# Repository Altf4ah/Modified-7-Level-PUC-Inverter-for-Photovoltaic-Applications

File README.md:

# Modified 7-Level PUC Inverter for Photovoltaic Applications

## Overview

This repository presents the design, simulation, and hardware implementation of a **Modified Seven-Level Packed U-Cell (MPUC) Inverter** for photovoltaic applications.

Multilevel inverters are widely used in renewable energy systems to convert DC power generated by solar panels into high-quality AC power suitable for loads or grid integration. Traditional inverter topologies such as Cascaded H-Bridge and Neutral Point Clamped inverters often require a large number of switches and components.

The **Modified Packed U-Cell (MPUC) inverter** provides a compact and efficient alternative by generating multiple voltage levels using fewer components while maintaining high power quality.

This project demonstrates both:

- Simulation validation of the proposed inverter topology
- Hardware implementation of a scaled prototype

---

# Project Objectives

The main objectives of this project are:

- Design a **Modified 7-Level PUC inverter topology**
- Implement **multicarrier SPWM control strategy**
- Validate the system through **simulation**
- Develop a **scaled hardware prototype**
- Analyse output voltage waveform and harmonic distortion

---

# Inverter Topology

The Modified PUC inverter is a **seven-level multilevel inverter topology** that uses:

- Two asymmetrical DC voltage sources
- Six switching devices
- A specialised switching sequence

The topology produces the following output voltage levels:

This multilevel output closely approximates a sinusoidal waveform, reducing harmonic distortion and improving power quality.

---

# Phase 1 — Simulation

The simulation phase validates the proposed inverter design before hardware implementation.

### Tools Used

- MATLAB
- Simulink

### Simulation Components

- MPUC inverter topology
- Multicarrier SPWM generation
- Switching algorithm
- Harmonic analysis

### Simulation Outputs

- 7-level output voltage waveform
- Load current waveform
- FFT analysis
- Total Harmonic Distortion (THD)

---

# Phase 2 — Hardware Implementation

A scaled hardware prototype was developed to validate the inverter performance.

### Hardware Modules

The hardware system consists of three main modules:

### 1. Power Supply Module

- Custom multi-tap transformer
- Bridge rectifier
- Filtering capacitors
- Provides isolated power for gate drivers

### 2. Driver Module

- Optocoupler-based isolation
- Gate driver circuits
- Signal amplification for MOSFET switching

### 3. Inverter Module

- Six MOSFET switches
- Two DC voltage sources
- Converts DC input into multilevel AC output

---

# Hardware Specifications

| Parameter | Value |
|--------|--------|
| Output Voltage | 45 V |
| Output Current | 1 A |
| Switching Devices | IRF540N MOSFET |
| Control Unit | Arduino |
| Driver IC | TLP350 |

---

# Control Strategy

The inverter switching signals are generated using an **Arduino-based control system** implementing a predefined switching table.

This generates the required sequence to produce the **seven-level output waveform**.

---

# PCB Design

The inverter and driver circuits were designed and implemented using:

- PCB layout design
- Copper board etching using ferric chloride
- Component soldering and testing

---

# Results

The results demonstrate that the Modified PUC inverter can generate a multilevel AC waveform with improved quality compared to conventional inverters.

Key outcomes:

- Successful generation of **7-level output voltage**
- Reduced harmonic distortion
- Efficient DC-AC conversion
- Successful hardware validation

---

# Applications

This inverter topology can be applied in:

- Solar photovoltaic systems
- Renewable energy converters
- Microgrid power systems
- Grid-connected inverter systems

---

## Repository Structure

- **Simulation/**
  - MATLAB / Simulink models

- **Hardware/**
  - Driver circuits
  - Inverter circuit
  - PCB design files

- **Arduino_Code/**
  - Switching control program

- **Images/**
  - Circuit diagrams
  - Simulation results
  - Hardware output waveforms

- **Documentation/**
  - Final project report
  - Presentation slides
---

# Authors

Final Year B.Tech Project.  
Department of Electrical Engineering.  
Govt. Model Engineering College, Thrikkakara.

- Althaf Ahmed   
- Daniel Charles  
- Aswathy V  
- Shaun George

---

# License

This project is published for **academic and research purposes**.

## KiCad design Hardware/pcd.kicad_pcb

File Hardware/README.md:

KiCad PCB project for a PUC inverter along with its driver board, designed as a single-layer layout and optimized for DIY etching.

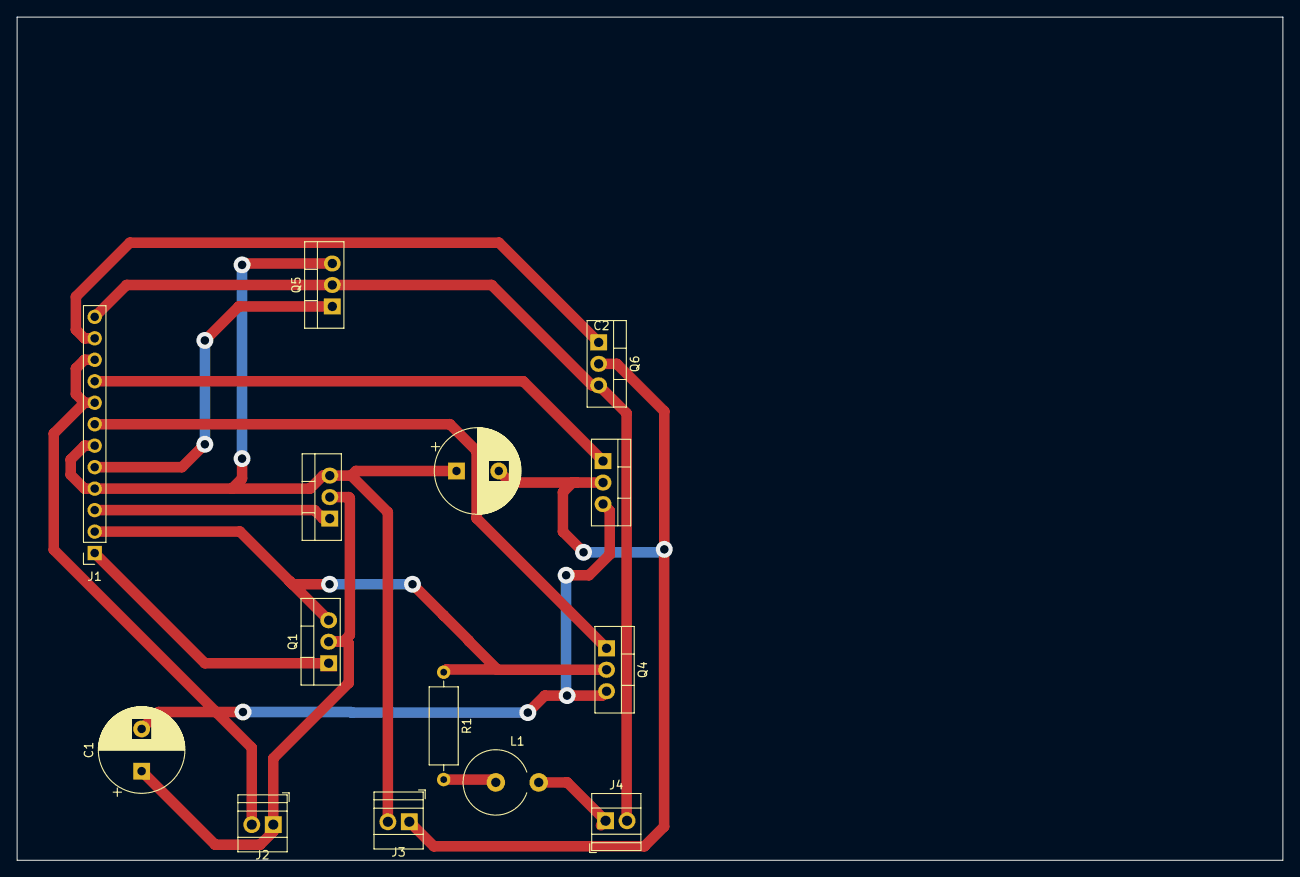
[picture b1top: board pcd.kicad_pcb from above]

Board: 2 copper layers, 149.7 x 99.7 mm, 14 parts (0 on the bottom side), 14 nets.

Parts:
C1, C2: C; CP_Radial_D10.0mm_P5.00mm
J1: Conn_01x12_Socket; PinSocket_1x12_P2.54mm_Vertical
J2, J3, J4: Screw_Terminal_01x02; TerminalBlock_Xinya_XY308-2.54-2P_1x02_P2.54mm_Horizontal
L1: L; L_Axial_L16.0mm_D7.5mm_P5.08mm_Vertical_Fastron_XHBCC
Q1, Q2, Q3, Q4, Q5, Q6: STGP7NC60HD; TO-220-3_Vertical
R1: R; R_Axial_DIN0309_L9.0mm_D3.2mm_P12.70mm_Horizontal

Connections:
/GRID+: J4.1, L1.2
/GRID-: J1.12, J4.2, Q5.2 (C), Q6.3 (E)
/T1: J1.1, Q1.1 (G)
/T1_g: J1.2, Q1.3 (E), Q4.2 (C), R1.1
/T2: J1.3, Q2.1 (G)
/T3: J1.5, Q5.1 (G)
/T4: J1.7, Q4.1 (G)
/T5: J1.9, Q3.1 (G)
/T6: J1.11, Q6.1 (G)
BUS1+: C1.1, J2.1, Q1.2 (C), Q2.2 (C)
BUS1-: C1.2, J1.8, J1.10, J2.2, Q3.3 (E), Q4.3 (E)
BUS2+: C2.2, J3.1, Q3.2 (C), Q6.2 (C)
BUS2-: C2.1, J1.4, J1.6, J3.2, Q2.3 (E), Q5.3 (E)
unnamed: L1.1, R1.2

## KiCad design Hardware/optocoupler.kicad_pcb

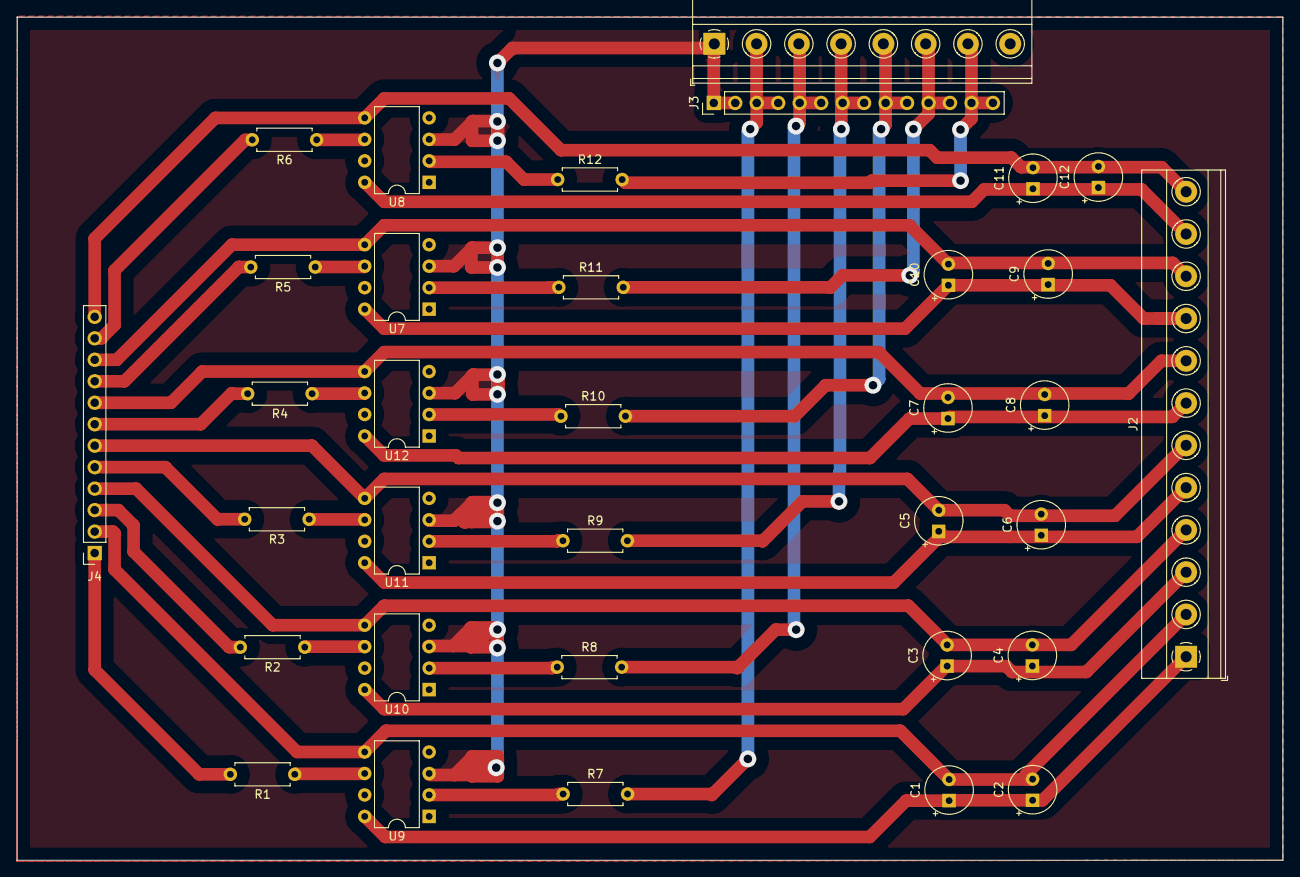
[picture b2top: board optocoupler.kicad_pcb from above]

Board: 2 copper layers, 149.7 x 99.7 mm, 34 parts (0 on the bottom side), 37 nets.

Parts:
C1, C2, C3, C4, C5, C6, C7, C8, C9, C10, C11, C12: C; CP_Radial_Tantal_D5.5mm_P2.50mm
J1: Screw_Terminal_01x07; TerminalBlock_Phoenix_MKDS-1,5-8_1x08_P5.00mm_Horizontal
J2: Conn_01x12_Socket; TerminalBlock_Phoenix_MKDS-1,5-12_1x12_P5.00mm_Horizontal
J3: Screw_Terminal_01x14; PinHeader_1x14_P2.54mm_Vertical
J4: Conn_01x12_Socket; PinSocket_1x12_P2.54mm_Vertical
R1, R2, R3, R4, R5, R6, R7, R8, R9, R10, R11, R12: R; R_Axial_DIN0207_L6.3mm_D2.5mm_P7.62mm_Horizontal
U7, U8, U9, U10, U11, U12: TLP250; DIP-8_W7.62mm

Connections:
/T1: R1.1, U9.6 (VO)
/T1_g: C1.2, C2.2, J2.2, J4.2, U9.5 (VEE)
/T1_i: J1.2, J3.3, J3.4, R7.2
/T2: R2.1, U10.6 (VO)
/T2_g: C3.2, C4.2, J2.4, J4.4, U10.5 (VEE)
/T2_i: J1.3, J3.5, J3.6, R8.2
/T3: R3.1, U11.6 (VO)
/T3_g: C5.2, C6.2, J2.6, J4.6, U11.5 (VEE)
/T3_i: J1.4, J3.7, J3.8, R9.2
/T4: R4.1, U12.6 (VO)
/T4_g: C7.2, C8.2, J2.8, J4.8, U12.5 (VEE)
/T4_i: J1.5, J3.9, J3.10, R10.2
/T5: R5.1, U7.6 (VO)
/T5_g: C9.2, C10.2, J2.10, J4.10, U7.5 (VEE)
/T5_i: J1.6, J3.11, J3.12, R11.2
/T6: R6.1, U8.6 (VO)
/T6_g: C11.2, C12.2, J2.12, J4.12, U8.5 (VEE)
/T6_i: J1.7, J3.13, J3.14, R12.2
/s1_i: C1.1, C2.1, J2.1, U9.8 (VCC)
/s2_i: C3.1, C4.1, J2.3, U10.8 (VCC)
/s3_i: C5.1, C6.1, J2.5, U11.8 (VCC)
/s4_i: C7.1, C8.1, J2.7, U12.8 (VCC)
/s5_i: C9.1, C10.1, J2.9, U7.8 (VCC)
/s6_i: C11.1, C12.1, J2.11, U8.8 (VCC)
GNDD: J1.1, J3.1, J3.2, U7.3 (C), U8.3 (C), U9.3 (C), U10.3 (C), U11.3 (C), U12.3 (C)
unnamed: J4.1, R1.2
unnamed: J4.3, R2.2
unnamed: J4.5, R3.2
unnamed: J4.7, R4.2
unnamed: J4.9, R5.2
unnamed: J4.11, R6.2
unnamed: R11.1, U7.2 (A)
unnamed: R12.1, U8.2 (A)
unnamed: R7.1, U9.2 (A)
unnamed: R8.1, U10.2 (A)
unnamed: R9.1, U11.2 (A)
unnamed: R10.1, U12.2 (A)

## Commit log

2026-03-07 Revise README for Modified 7-Level PUC Inverter project
    Updated the README to provide a comprehensive overview of the Modified 7-Level PUC inverter project, including objectives, topology, simulation, hardware implementation, specifications, control strat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
2026-03-08 Revise repository structure in README.md
    Updated repository structure section with improved formatting and additional details.
2026-03-08 README
2026-03-08 PCB design
2026-03-08 switching code
2026-03-08 Circuit diagram
2026-03-19 oltage Updates
    Removed voltage level output table from README.
2026-03-19 Voltage updaged
2026-03-19 README.md
    Corrected spelling of 'specialized' to 'specialised'.
